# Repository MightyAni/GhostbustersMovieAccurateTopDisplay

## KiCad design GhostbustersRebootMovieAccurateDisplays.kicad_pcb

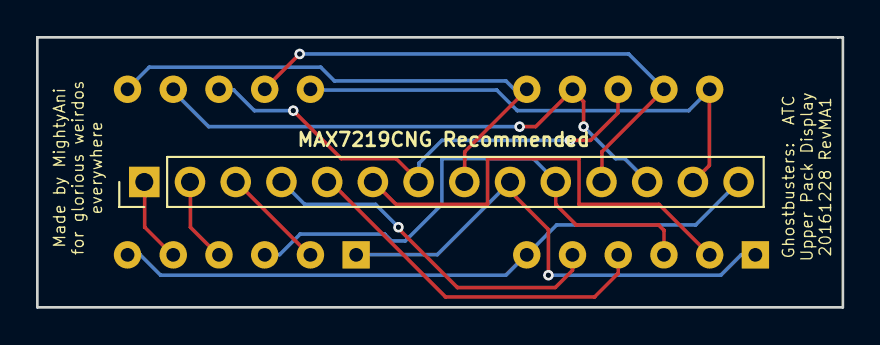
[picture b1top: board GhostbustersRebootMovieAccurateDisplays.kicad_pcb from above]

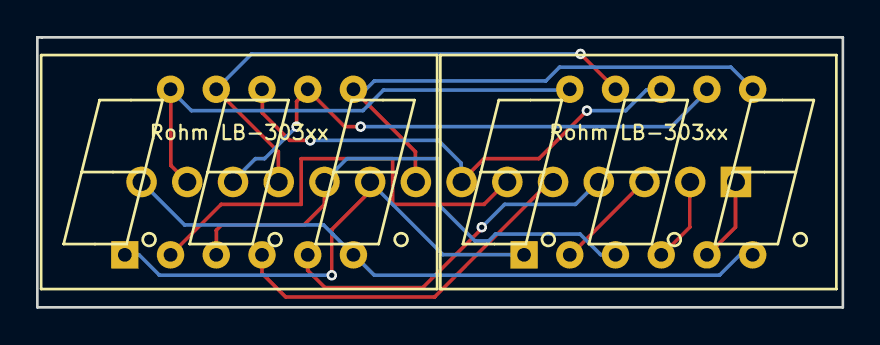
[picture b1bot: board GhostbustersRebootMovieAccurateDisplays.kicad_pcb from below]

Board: 2 copper layers, 44.8 x 15.0 mm, 3 parts (2 on the bottom side), 14 nets.

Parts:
AFF1, AFF2: Rohm LB-303xx; MovieAccurateTopDisp
PH1: CONN_01X14; Pin_Header_Straight_1x14_Pitch2.54mm

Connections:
unnamed: AFF1.1, AFF2.1, PH1.9
unnamed: AFF1.2, PH1.6
unnamed: AFF1.3, AFF2.3, PH1.10
unnamed: AFF1.4, PH1.5
unnamed: AFF1.5, PH1.4
unnamed: AFF1.6, AFF2.6, PH1.14
unnamed: AFF1.7, AFF2.7, PH1.8
unnamed: AFF1.8, AFF2.8, PH1.12
unnamed: AFF1.9, AFF2.9, PH1.7
unnamed: AFF1.10, AFF2.10, PH1.11
unnamed: AFF1.11, AFF2.11, PH1.13
unnamed: AFF2.2, PH1.3
unnamed: AFF2.4, PH1.2
unnamed: AFF2.5, PH1.1
